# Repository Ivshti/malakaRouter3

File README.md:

# malakaRouter3

**A fine-pitch escape/fanout generator for KiCad, built to close the exact gap
that stalls automated routing on very dense connectors and packages: getting
every pin out to open copper using *only standard-spec vias* — no via-in-pad,
no sub-spec drill/annular escalation — even when a straight-line escape is
blocked by neighboring copper.**

It is not a full autorouter. It solves one specific, hard sub-problem — the
fine-pitch escape — and is designed to be the first stage of a pipeline in
front of a general-purpose router. This repo pairs with
[KiCadRoutingTools](https://github.com/drandyhaas/KiCadRoutingTools), which
handles everything *around* that sub-problem: bulk point-to-point routing,
BGA/QFN fanout, plane/zone repair, and DRC-oracle validation. Together they
route boards that neither tool closes alone.

## Why this exists

Modern boards increasingly carry WLCSP, micro-BGA, and dense micro-connector
packages at 0.4 mm pitch or tighter, with 0.2 mm pads. At that scale, a
standard 0.45 mm via often cannot physically fit under or between the pads —
so most automated fanout tools (including KiCadRoutingTools' own
`bga_fanout.py`) fall back to a smaller, sub-spec via (e.g. 0.25 mm/0.15 mm
drill) with a warning, because *some* legal via site genuinely doesn't exist
right at the pad.

But "no legal via site at the pad" and "no legal via site nearby" are
different claims. Very often a pin that's boxed in at zero offset has a
completely legal standard-via site 0.3–1.5 mm away, reachable by a short jog
around whatever's in the way (a neighboring pad, another pin's own escape
stub, a stitching via). `escape_gen.py` searches for exactly that: it walks
outward from each pin, in rings and increasing radii, checking every
candidate site against every real obstacle nearby (not just the pin's own
footprint — existing traces, vias, and other pads within range), and only
emits a via where the standard geometry actually verifies clean. When it
can't find one, it says so explicitly rather than silently degrading to a
smaller via or leaving the pin abandoned.

This was built and proven closing out real, otherwise-stuck escapes on a
complex CM5-based carrier board carrying multiple 0.4 mm-pitch WLCSP sensor
packages and micro-connectors — cases where the fine-pitch escape was the last
blocker standing between a fully-populated board and full autorouting.

## What's in this repo

| File | Purpose |
|---|---|
| `escape_gen.py` | The escape generator. Two modes: connector escape (`--ref`) and single-pad power/plane taps (`--power-taps`). |
| `refill_zones.py` | Scoped zone refill (only zones near a point) — avoids the whack-a-mole a full-board refill can trigger on a large, densely-zoned board. |
| `cleanup_dangling.py` | DRC-driven removal of dangling stubs/vias and redundant stitching vias, iterated against `kicad-cli` until stable. |
| `examples/gen_demo_board.py` | Generates a small synthetic demo board (below) — no real project data. |
| `examples/demo_board.kicad_pcb` | The pre-generated demo board, ready to route. |

`r3/` contains an in-progress, experimental topological-routing research
prototype (constrained-Delaunay corridor graph + negotiated congestion). It is
**not** part of the proven workflow this README documents and is validated
only on tiny synthetic fixtures so far — see its own docstrings if you're
curious, but don't expect it to route anything real yet.

## Requirements

- **KiCad 9 or 10** with `kicad-cli` on `PATH` (the DRC oracle — every step
  below is validated against it, never a heuristic).
- **KiCad's own Python** (has the `pcbnew` module) for `refill_zones.py` and
  `examples/gen_demo_board.py`. On macOS this is typically
  `/Applications/KiCad/KiCad.app/Contents/Frameworks/Python.framework/Versions/Current/bin/python3`.
  `escape_gen.py` and `cleanup_dangling.py` need only a normal Python 3 (no
  `pcbnew` import) plus `kicad-cli` on `PATH`.
- **[KiCadRoutingTools](https://github.com/drandyhaas/KiCadRoutingTools)**
  cloned as a sibling directory (`../KiCadRoutingTools` relative to this repo)
  — `escape_gen.py` imports its `kicad_parser`/`kicad_writer` modules for file
  I/O, and the workflow below calls its `bga_fanout.py`, `route.py`, and
  `route_disconnected_planes.py` directly. Follow that repo's own setup
  instructions (`python build_router.py` to fetch/build its Rust core) before
  using the combo workflow.

## Quick start: reproduce the demo end to end

The demo board (`examples/demo_board.kicad_pcb`) is a small synthetic fixture:
one fine-pitch connector `J1` (staggered 2-row, 0.4 mm pitch within each row,
0.2 mm pads — the same proportions as the real hardware this was proven on)
carrying a power net and two signal nets, plus two target components (`U1`,
`U2`) elsewhere on the board that those nets need to reach. Regenerate it
anytime with `python3 examples/gen_demo_board.py` (KiCad's Python).

```sh
cd malakaRouter3
KICAD_PY=/Applications/KiCad/KiCad.app/Contents/Frameworks/Python.framework/Versions/Current/bin/python3

# 1. Escape the fine-pitch connector: standard vias only, verified against
#    every real obstacle nearby (not just J1's own footprint).
python3 escape_gen.py examples/demo_board.kicad_pcb /tmp/1_escaped.kicad_pcb --ref J1
cp examples/demo_board.kicad_pro /tmp/1_escaped.kicad_pro

# 2. Hand off to KiCadRoutingTools' route.py to finish the point-to-point
#    connections from the escape stubs to their targets. escape_gen's output
#    is ordinary KiCad copper, so any KiCad-aware router can pick it up from
#    here -- this is the actual combo: escape_gen owns the hard fine-pitch
#    part, route.py owns the easy open-space bulk routing.
cd ../KiCadRoutingTools
python3 route.py /tmp/1_escaped.kicad_pcb /tmp/2_routed.kicad_pcb \
  PWR GND SIG_A SIG_B \
  --track-width 0.13 --clearance 0.125 --via-size 0.45 --via-drill 0.2 \
  --hole-to-hole-clearance 0.2 --layers F.Cu B.Cu
cd -
cp examples/demo_board.kicad_pro /tmp/2_routed.kicad_pro

# 3. Refill zones and check with the DRC oracle -- the only authority that
#    matters. kicad-cli's own --refill-zones is correct for almost every case.
kicad-cli pcb drc --exit-code-violations --refill-zones --save-board \
  /tmp/2_routed.kicad_pcb -o /tmp/final.rpt

# 4. If DRC flags dangling stubs/vias (routers occasionally leave a few after
#    a rescue/rip-up pass), sweep them and re-check.
python3 cleanup_dangling.py /tmp/2_routed.kicad_pcb /tmp/3_final.kicad_pcb \
  examples/demo_board.kicad_pro
kicad-cli pcb drc --exit-code-violations --refill-zones \
  /tmp/3_final.kicad_pcb -o /tmp/final.rpt
```

Running this exactly reproduces: 0 unconnected items, no sub-spec vias, only
cosmetic silkscreen warnings left (default reference-designator placement —
harmless, unrelated to routing).

## The full workflow (what to reach for, and when)

This is the methodology, generalized from what actually closed the real
board. Not every step is needed every time — use judgment per board.

1. **Survey first.** Copy the board (never touch the original — every step
   below writes a new file). Run `kicad-cli pcb drc --exit-code-violations
   --refill-zones` for the true baseline: unconnected count, violation
   breakdown, and which are pre-existing vs. introduced by later steps (diff
   later reports against this baseline by matching `[category]` + coordinates
   — an unrelated violation identical to baseline is not yours to fix).

2. **Fine-pitch/BGA-style packages: try `bga_fanout.py` first** (from
   KiCadRoutingTools) for genuinely 2D/radial pad grids (WLCSP, BGA, QFN). Its
   escape-direction handling is built for that topology.
   `escape_gen.py --ref` is built for *directional* connectors instead —
   footprints whose own anchor point sits offset from the pad field in a
   consistent direction (true of most real connector footprints, since the
   anchor is usually at the part's body/shell). It computes each pin's escape
   direction from that anchor→pad-field vector, so it degenerates on a
   perfectly radially-symmetric footprint anchored at its own pad centroid
   (see **Limitations**). When a directional connector's escape needs
   standard-vias-only guarantees `bga_fanout.py` doesn't give you, or when
   `bga_fanout.py`'s own escape leaves specific pins isolated, run
   `escape_gen.py --ref CONNECTOR_REF` on it directly.

3. **Single fine-pitch power/ground pads that need a plane tap** (not a full
   connector escape — one pad at a time, e.g. a BGA's own VCC ball): use
   `escape_gen.py --power-taps "REF.PAD,REF.PAD,..."`. It tries via-in-pad
   first, then spirals outward for a standard-via site with a clear stub,
   including a 1-bend waypoint fallback for pads boxed in by a sibling pin's
   own escape copper. If no standard-via site exists at all within its search
   radius, it fails that pad honestly rather than emitting sub-spec geometry —
   that pad may need a genuinely different fix (nudging a neighboring net's
   trace, widening local pitch), which is a design decision, not something to
   route around silently.

4. **Bulk / point-to-point completion: `route.py`** (KiCadRoutingTools). One
   thing worth knowing before you hit it: if a net needs a very long
   point-to-point run (tens of mm across a busy board) *and* you route it
   together with several other nets in one call, it can exhaust its search
   budget fighting for the same iterations as the others and fail — while the
   exact same net, routed **alone** first with the same budget, succeeds
   easily. If a net fails only when bundled with others, try it solo first,
   then layer the remaining nets onto that result in a second `route.py` call
   (`filter_already_routed` skips what's already connected, so this composes
   cleanly). This one change turns "can't find a route" into "found it in
   under 200k iterations" with no parameter changes at all.

5. **Zone/plane connectivity gaps** (a GND/power pad or a whole isolated
   copper region not reaching its pour, usually surfaced by DRC as
   `unconnected_items` between two zone fragments or a pad and a zone): use
   KiCadRoutingTools' `route_disconnected_planes.py --nets NET --plane-layers
   LAYER`. It finds disconnected regions of a net's plane and bridges them
   with tracks/vias, with its own DRC-oracle recheck loop.

6. **Refill zones.** `kicad-cli pcb drc --refill-zones --save-board` is the
   right tool for almost every case — it matches KiCad's own "Refill All
   Zones." Reach for `refill_zones.py`'s scoped refill only if a full-board
   refill introduces a new violation somewhere unrelated to what you actually
   changed (happens occasionally on boards with many zones — refilling
   *everything* can nondeterministically resolve one marginal pre-existing
   zone-boundary case while exposing a different one elsewhere; refilling only
   the zones near your change avoids disturbing the rest of the board).

7. **Sweep dangling copper.** `cleanup_dangling.py` — iterates
   `track_dangling`/`via_dangling`/GND-`hole_clearance` removal against the
   DRC oracle until stable.

8. **The DRC oracle is the only authority, always.** Every step above is
   judged by `kicad-cli pcb drc`, with the project's own `.kicad_pro` sibling
   present (board-specific rules — netclasses, min clearance/track/via floors
   — live there; a bare `.kicad_pcb` DRC'd without it will report the wrong
   thing). Never accept "looks routed" — check.

## How `escape_gen.py` works, briefly

- **Exact geometry, not a grid.** Every clearance check is analytic distance
  math (point-to-segment, segment-to-segment) against the real shapes
  involved — pad rectangles, via/track circles, existing copper — with a small
  safety margin over the board's stated clearance rule. No rasterization, so
  no half-cell over-blocking.
- **Obstacle-aware, including copper the tool didn't place.** Candidate via
  and stub sites are checked against every nearby pad, via, *and existing
  track segment* — not just the target footprint's own pads. (An earlier
  version only modeled pads/vias, which let a stub drive straight through an
  already-routed trace; fixed by making every check segment-aware.)
- **Never sub-spec.** All geometry uses one fixed, standard fab tier (0.13 mm
  track / 0.125 mm clearance / 0.45 mm via / 0.2 mm drill by default,
  configurable). If no legal site exists at that tier, the pin is reported as
  failed — never silently downgraded.
- **Search strategy:** ring search outward from each pin/pad (increasing
  radius, all angles) for a legal via site with a clear straight stub; if the
  straight stub is blocked, a 1-bend waypoint search (bend near the pin,
  perpendicular offset) finds a path around whatever's in the way. For a
  multi-pin connector, front-row pins (closest to the board interior, no via
  needed) are committed first so their stubs become obstacles the back row's
  search correctly respects.

## Layer direction discipline

Manual routers commonly bias each copper layer toward a consistent direction —
often diagonal, with adjacent layers running opposite diagonals — rather than
letting each net find whatever angle is locally shortest. The reason isn't
cosmetic: it keeps any two adjacent layers from running long parallel stretches
in the same direction (which is what couples them), and it makes via
transitions and DRC review predictable to eyeball, since a trace's layer is
recognizable from its angle alone.

KiCadRoutingTools' `route.py` already does an orthogonal version of this by
default, whether or not you ask for it: `direction_preference_cost` defaults to
`50` (nonzero = enabled), and `get_layer_direction_preferences()` assigns each
layer an alternating horizontal/vertical preference by layer index (F.Cu
horizontal, In1.Cu vertical, In2.Cu horizontal, B.Cu vertical, ...), penalizing
routes that go against their layer's preferred axis. Every `route.py` call in
the workflow above benefits from this without any extra flags — it's why
routed boards already show a visible per-layer directional tendency.

That cost is deliberately small relative to the router's other costs —
`TURN_COST` and `CROSSING_PENALTY` are both `1000`, twenty times
`DIRECTION_PREFERENCE_COST`'s `50` (the same order as `VIA_COST`). So it acts
as a **tiebreaker between otherwise-equal paths**, not a dominant steering
force: a genuinely shorter or lower-via route still wins even against its
layer's grain. This mirrors the same design choice other PCB tooling (e.g.
atopile) makes for the identical reason — a hard directional bias would fight
the router's actual job (shortest legal path) on every board where the
"wrong-grain" route is meaningfully better; a tiebreaker only kicks in when the
router would otherwise be indifferent.

What isn't modeled yet is true diagonal preference (opposite 45°/135° per
layer, rather than orthogonal H/V). The router's pathfinding is octolinear (45°
jogs are already part of how it connects two points), but the preference-cost
mechanism only recognizes horizontal, vertical, or no preference — not a
specific diagonal orientation. Formalizing that as the same kind of low-weight
tiebreaker (alternating +45°/-45° instead of H/V) is a reasonable next step,
given how directly it matches established manual-routing practice.

## Limitations

- **Directional connectors only for `--ref`.** The escape-direction heuristic
  is `normalize(pad_field_centroid - footprint_anchor)`. This matches how most
  real connector footprints are authored (anchor near the body/shell, offset
  from the pads) but fails on a footprint anchored exactly at its own pad
  centroid, or on genuinely radial 2D grids (BGA/WLCSP) — use
  `bga_fanout.py` for those instead (step 2 above).
- **No multi-pin/Steiner routing.** `--power-taps` handles one pad at a time;
  connector escape handles one connector's pins independently. Tying multiple
  same-net pads *within* the escaped footprint together (e.g. bridging a
  package's own split power pins) is a separate step — route it with
  `route.py` afterward, same as any other net.
- **Single-layer-pair (F.Cu/B.Cu) by default.** Inner-layer escapes aren't
  modeled.
- **GND/GNDPWR pins are skipped** in connector-escape mode (assumed
  plane-tied elsewhere) — use `--power-taps` if a specific ground pad genuinely
  needs an explicit tap.

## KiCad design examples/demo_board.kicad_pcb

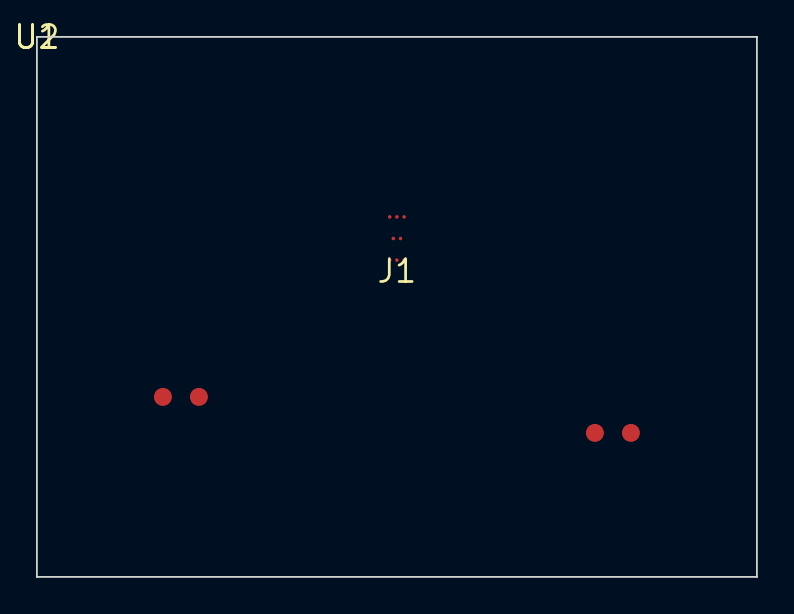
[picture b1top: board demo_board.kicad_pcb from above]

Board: 2 copper layers, 40.0 x 30.0 mm, 3 parts (0 on the bottom side), 4 nets, no tracks yet.

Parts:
J1: (no value)
U1, U2: (no value)

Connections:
GND: J1.C1, J1.C2, J1.C3, U2.2
PWR: J1.A1, J1.A3, J1.B1, U1.2
SIG_A: J1.A2, U1.1
SIG_B: J1.B2, U2.1
